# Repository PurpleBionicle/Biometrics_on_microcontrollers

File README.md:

<h1> Биометрический считыватель</h1>>
Программа имеет 2 режима: <br>
1) аутентификация - по поступающему видео перебирает датасет<br>
датасет представляет собой зашифрованную БД <br>
2) регистрация - записывается видео и из него берутся фото для датасета <br>
Оба режима поддерживают ip-камеры с помощью протокола rtsp <br>
Распознование сделано на opencv2 + face-recognition<br>
Также добавлена возможность проверки на liveness. Проверка осуществляется через фильтры Хаара, 
1 умеет определять только открытые глаза, другой открытые и закрытые <br>
Проект по Аппаратным средствам, так что тут же и разводка ПП / сборочный чертеж<br>
Пара фото: <br>

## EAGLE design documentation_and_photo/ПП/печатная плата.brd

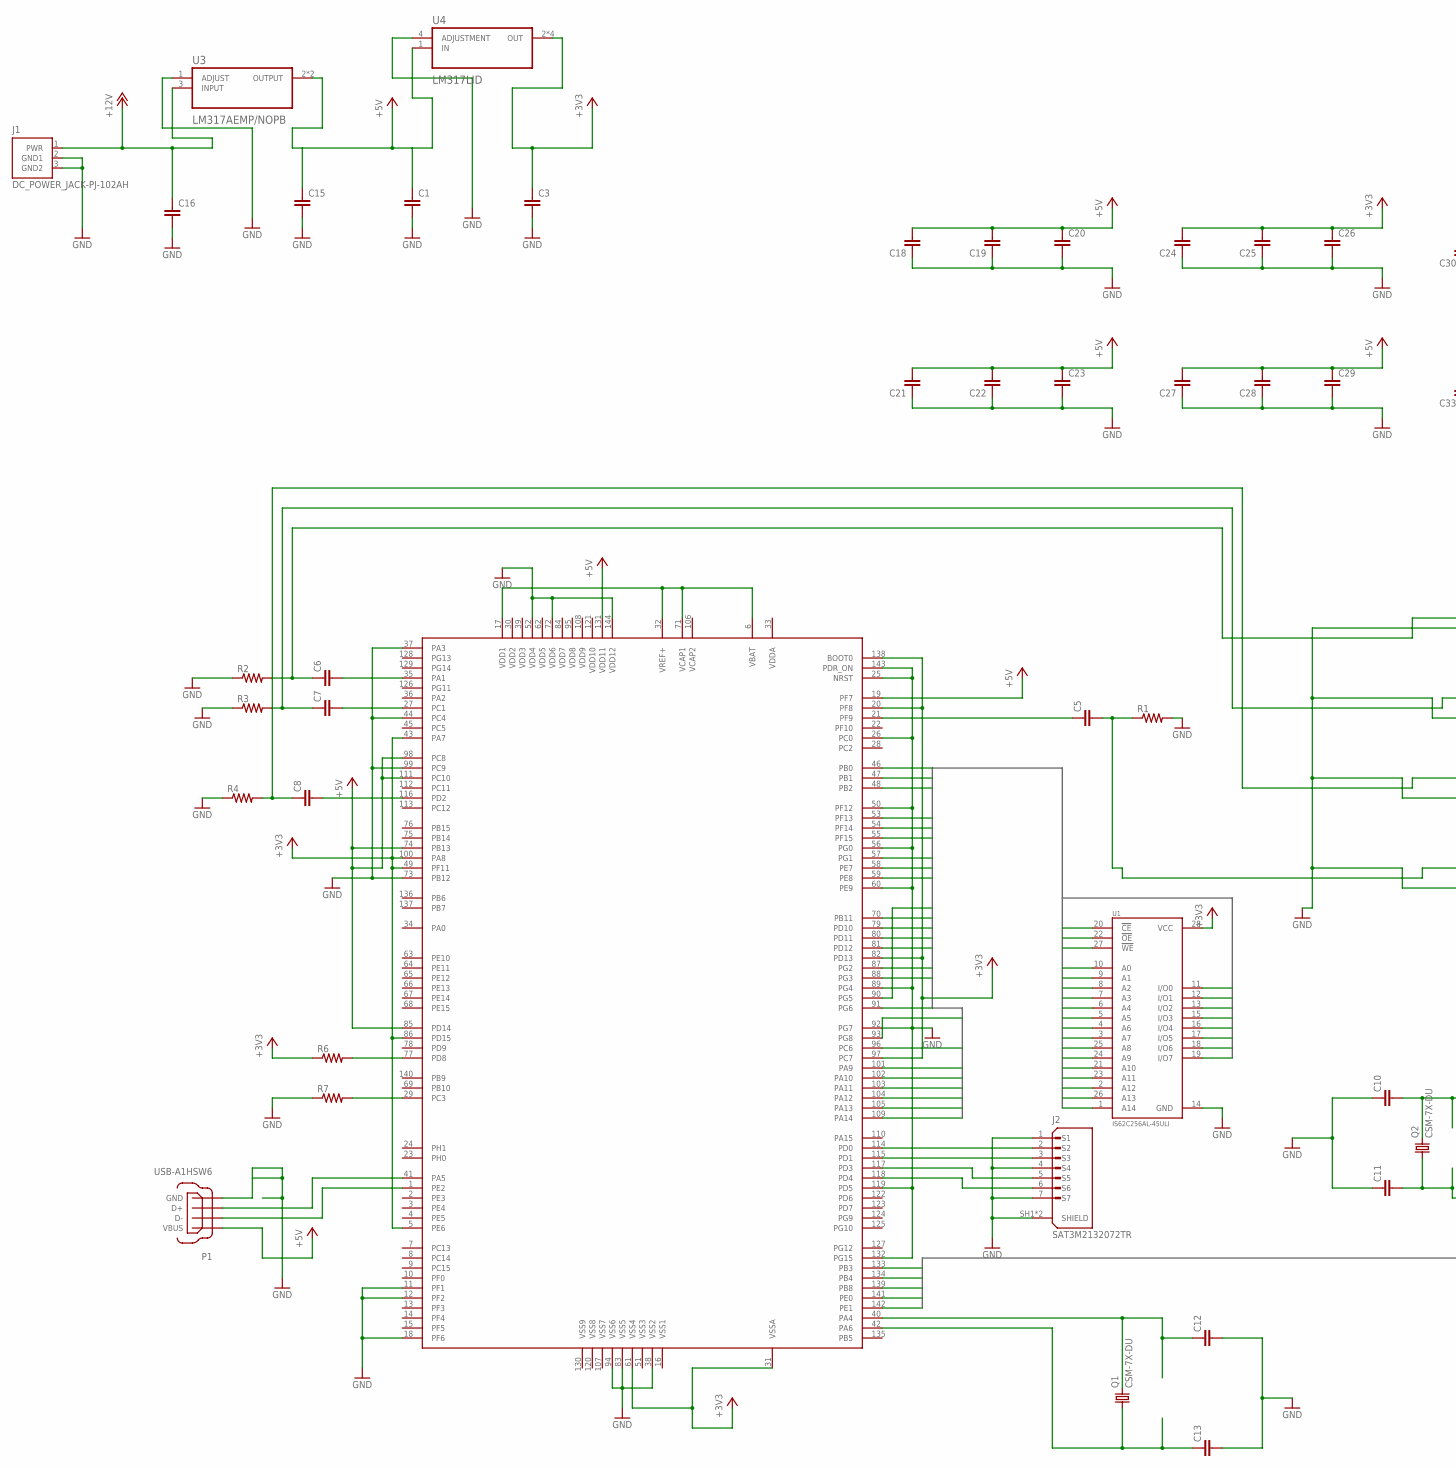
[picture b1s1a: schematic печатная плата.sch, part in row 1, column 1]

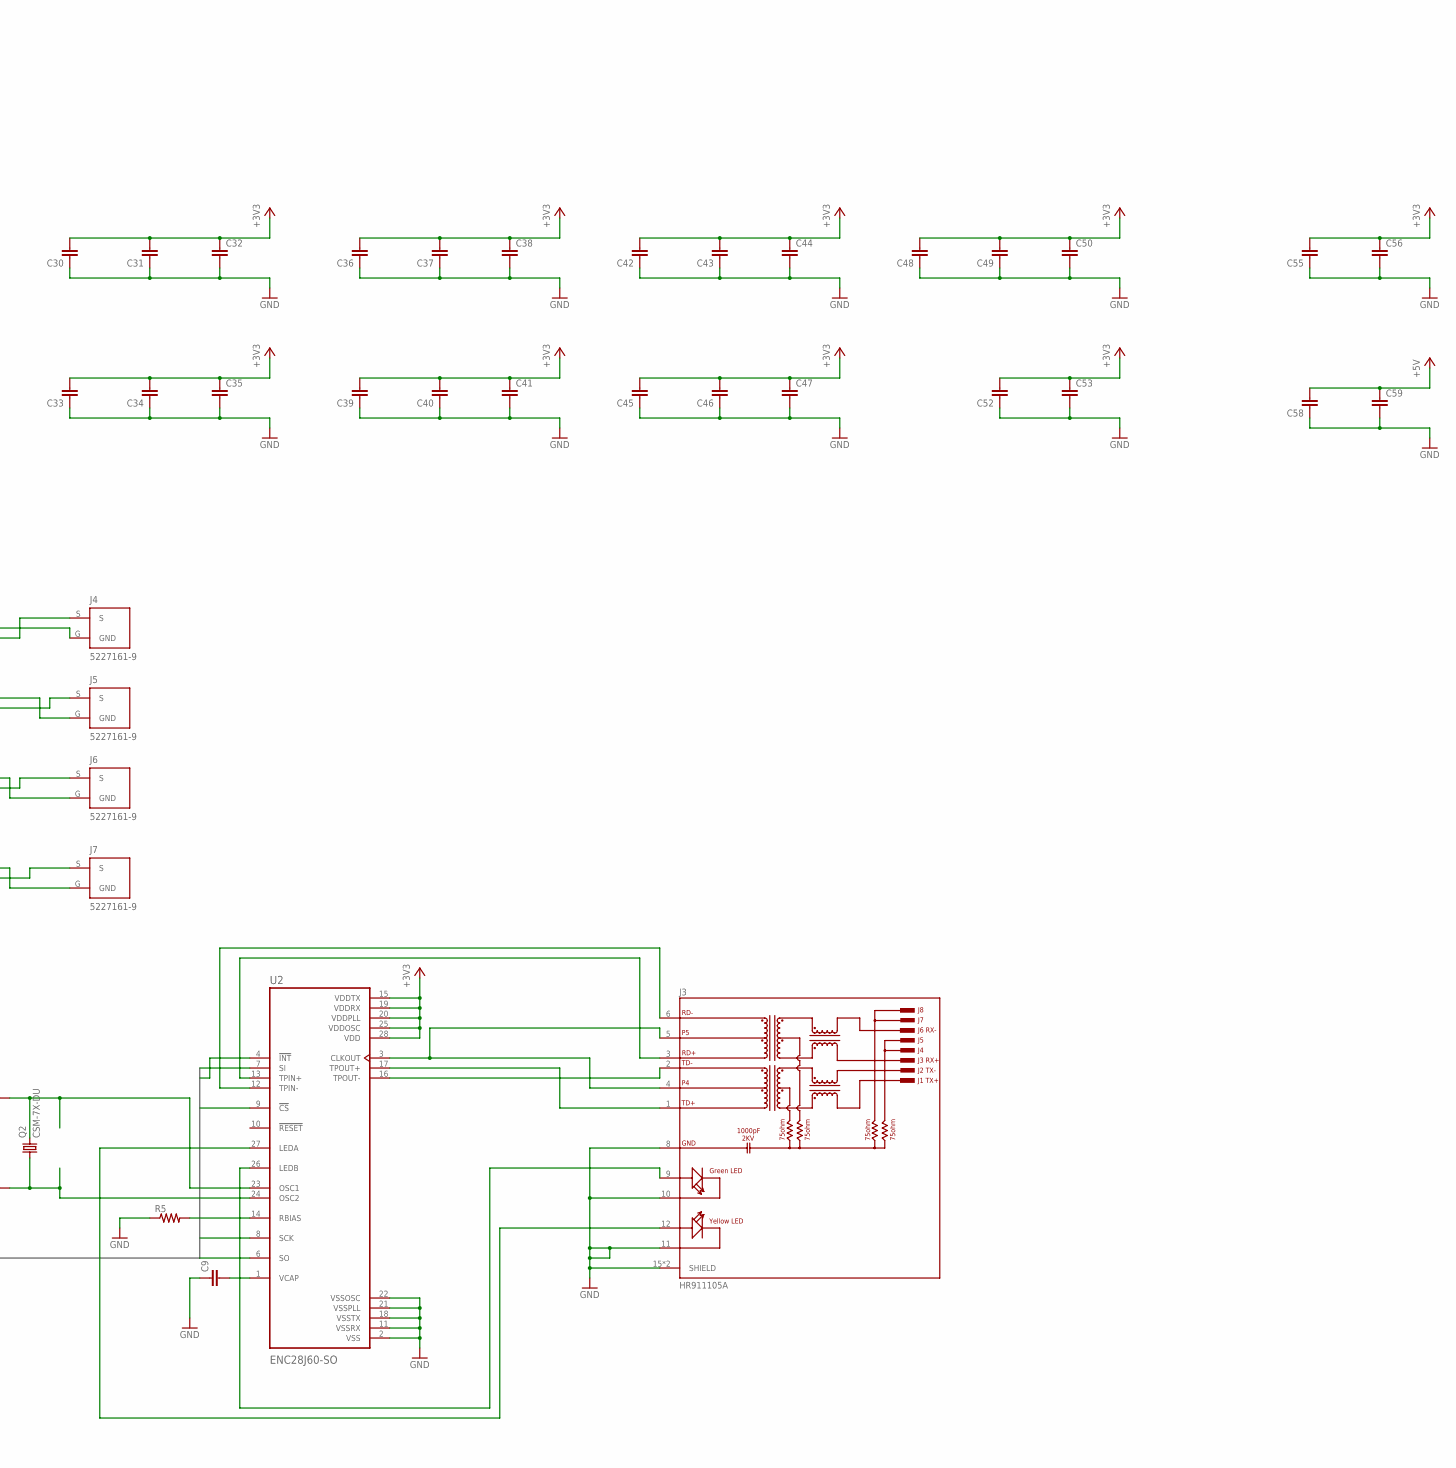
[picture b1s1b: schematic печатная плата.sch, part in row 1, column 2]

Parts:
C1, C3, C5, C6, C7, C8, C9, C10, C11, C12, C13, C15, C16, C18, C19, C20, C21, C22, C23, C24, C25, C26, C27, C28, C29, C30, C31, C32, C33, C34, C35, C36, C37, C38, C39, C40, C41, C42, C43, C44, C45, C46, C47, C48, C49, C50, C52, C53, C55, C56, C58, C59: C_0201; 0201
J1: DC_POWER_JACK-PJ-102AH; PJ-102AH
J2: SAT3M2132072TR; AMPHENOL_SAT3M2132072TR
J3: HR911105A; HANRUN_HR911105A
J4, J5, J6, J7: 5227161-9; TE_5227161-9
P1: USB-A1HSW6; OST_USB-A1HSW6
Q1, Q2: CSM-7X-DU
R1, R2, R3, R4, R5, R6, R7: R-US_M1406; M1406
U1: IS62C256AL-45ULI; SOIC127P1210X305-28N
U2: ENC28J60-SO; SOIC127P1030X265-28N
U3: LM317AEMP/NOPB; SOT230P700X180-4N
U4: LM317LID; SOIC127P599X175-8N
U$1: STM32F4Z_144PIN; LQFP144

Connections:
+3V3: C3.1, C24.2, C25.2, C26.1, C30.2, C31.2, C32.1, C33.2, C34.2, C35.1, C36.2, C37.2, C38.1, C39.2, C40.2, C41.1, C42.2, C43.2, C44.1, C45.2, C46.2, C47.1, C48.2, C49.2, C50.1, C52.2, C53.1, C55.2, C56.1, R6.1, U1.28 (VCC), U2.15 (VDDTX), U2.19 (VDDRX), U2.20 (VDDPLL), U2.25 (VDDOSC), U2.28 (VDD), U4.2 (OUT), U4.3 (OUT), U4.6 (OUT), U4.7 (OUT), U$1.5 (PE6), U$1.20 (PF8), U$1.31 (VSSA), U$1.43 (PA7), U$1.49 (PF11), U$1.61 (VSS4), U$1.82 (PD13), U$1.86 (PD15), U$1.97 (PC7), U$1.100 (PA8), U$1.138 (BOOT0)
+5V: C1.1, C18.2, C19.2, C20.1, C21.2, C22.2, C23.1, C27.2, C28.2, C29.1, C58.2, C59.1, P1.1 (VBUS), U3.2 (OUTPUT), U3.4 (OUTPUT), U4.1 (IN), U$1.19 (PF7), U$1.74 (PB13), U$1.85 (PD14), U$1.98 (PC8), U$1.111 (PC10), U$1.131 (VDD11)
+5V1: C15.1
+12V: C16.1, J1.1 (PWR), U3.3 (INPUT)
A1: U2.6 (SO), U$1.133 (PB3)
A2: U2.8 (SCK), U$1.134 (PB4)
A3: U2.9 (!CS), U$1.139 (PB8)
A4: U2.7 (SI), U$1.141 (PE0)
A5: U2.4 (!INT), U$1.142 (PE1)
D0: U$1.46 (PB0)
D1: U1.20 (!CE)
D2: U1.22 (!OE), U$1.47 (PB1), U$1.48 (PB2)
D3: U1.27 (!WE), U$1.53 (PF13)
D4: U1.10 (A0), U$1.54 (PF14)
D5: U1.9 (A1), U$1.55 (PF15)
D6: U1.8 (A2), U$1.57 (PG1)
D7: U1.7 (A3), U$1.58 (PE7)
D8: U1.6 (A4), U$1.59 (PE8)
D9: U1.5 (A5), U$1.70 (PB11)
D10: U1.4 (A6), U$1.79 (PD10)
D11: U1.3 (A7), U$1.80 (PD11)
D12: U1.25 (A8), U$1.81 (PD12)
D13: U1.24 (A9), U$1.87 (PG2)
D14: U1.21 (A10), U$1.88 (PG3)
D15: U1.23 (A11)
D16: U1.2 (A12), U$1.91 (PG6)
D17: U1.26 (A13), U$1.93 (PG8)
D18: U1.1 (A14), U$1.96 (PC6)
D19: U1.11 (I/O0), U$1.101 (PA9)
D20: U1.12 (I/O1)
D21: U1.13 (I/O2), U$1.102 (PA10)
D22: U1.15 (I/O3), U$1.103 (PA11)
D23: U1.16 (I/O4), U$1.104 (PA12)
D24: U1.17 (I/O5), U$1.105 (PA13)
D25: U1.18 (I/O6), U$1.109 (PA14)
D26: U1.19 (I/O7), U$1.90 (PG5)
GND: C1.2, C3.2, C9.1, C10.1, C11.1, C12.2, C13.2, C15.2, C16.2, C18.1, C19.1, C20.2, C21.1, C22.1, C23.2, C24.1, C25.1, C26.2, C27.1, C28.1, C29.2, C30.1, C31.1, C32.2, C33.1, C34.1, C35.2, C36.1, C37.1, C38.2, C39.1, C40.1, C41.2, C42.1, C43.1, C44.2, C45.1, C46.1, C47.2, C48.1, C49.1, C50.2, C52.1, C53.2, C55.1, C56.2, C58.1, C59.2, J1.2 (GND1), J1.3 (GND2), J2.1 (S1), J2.4 (S4), J2.7 (S7), J2.SH1 (SHIELD), J2.SH2 (SHIELD), J3.8 (GND), J3.10 (GC), J3.11 (YC), J3.15 (SHIELD), J3.16 (SHIELD), J4.G (GND), J5.G (GND), J6.G (GND), J7.G (GND), P1.4 (GND), R1.2, R2.1, R3.1, R4.1, R5.1, R7.1, U1.14 (GND), U2.2 (VSS), U2.11 (VSSRX), U2.18 (VSSTX), U2.21 (VSSPLL), U2.22 (VSSOSC), U3.1 (ADJUST), U4.4 (ADJUSTMENT), U$1.11 (PF1), U$1.12 (PF2), U$1.18 (PF6), U$1.25 (NRST), U$1.26 (PC0), U$1.37 (PA3), U$1.38 (VSS2), U$1.44 (PC4), U$1.50 (PF12), U$1.52 (VDD4), U$1.56 (PG0), U$1.60 (PE9), U$1.72 (VDD6), U$1.73 (PB12), U$1.83 (VSS5), U$1.89 (PG4), U$1.92 (PG7), U$1.94 (VSS6), U$1.99 (PC9), U$1.119 (PD5), U$1.132 (PG15), U$1.143 (PDR_ON), U$1.144 (VDD12)
unnamed: C5.2, J7.S, R1.1
unnamed: U$1.6 (VBAT), U$1.17 (VDD1), U$1.32 (VREF+), U$1.71 (VCAP1)
unnamed: C6.1, J4.S, R2.2
unnamed: C7.1, J5.S, R3.2
unnamed: C8.1, J6.S, R4.2
unnamed: J2.2 (S2), U$1.114 (PD0)
unnamed: C6.2, U$1.35 (PA1)
unnamed: C7.2, U$1.27 (PC1)
unnamed: C8.2, U$1.116 (PD2)
unnamed: C5.1, U$1.21 (PF9)
unnamed: J2.3 (S3), U$1.115 (PD1)
unnamed: J2.5 (S5), U$1.117 (PD3)
unnamed: J2.6 (S6), U$1.118 (PD4)
unnamed: J3.2 (TD-), U2.16 (TPOUT-)
unnamed: J3.1 (TD+), U2.17 (TPOUT+)
unnamed: J3.3 (RD+), U2.13 (TPIN+)
unnamed: J3.6 (RD-), U2.12 (TPIN-)
unnamed: C9.2, U2.1 (VCAP)
unnamed: C12.1, Q1.2, U$1.40 (PA4)
unnamed: C11.2, Q2.1, U2.24 (OSC2)
unnamed: C10.2, Q2.2, U2.23 (OSC1)
unnamed: C13.1, Q1.1, U$1.42 (PA6)
unnamed: R5.2, U2.14 (RBIAS)
unnamed: R7.2, U$1.29 (PC3)
unnamed: J3.4, J3.5, U2.3 (CLKOUT)
unnamed: R6.2, U$1.77 (PD8)
unnamed: P1.3 (D+), U$1.41 (PA5)
unnamed: P1.2 (D-), U$1.1 (PE2)
unnamed: J3.9 (GA), U2.26 (LEDB)
unnamed: J3.12 (YA), U2.27 (LEDA)

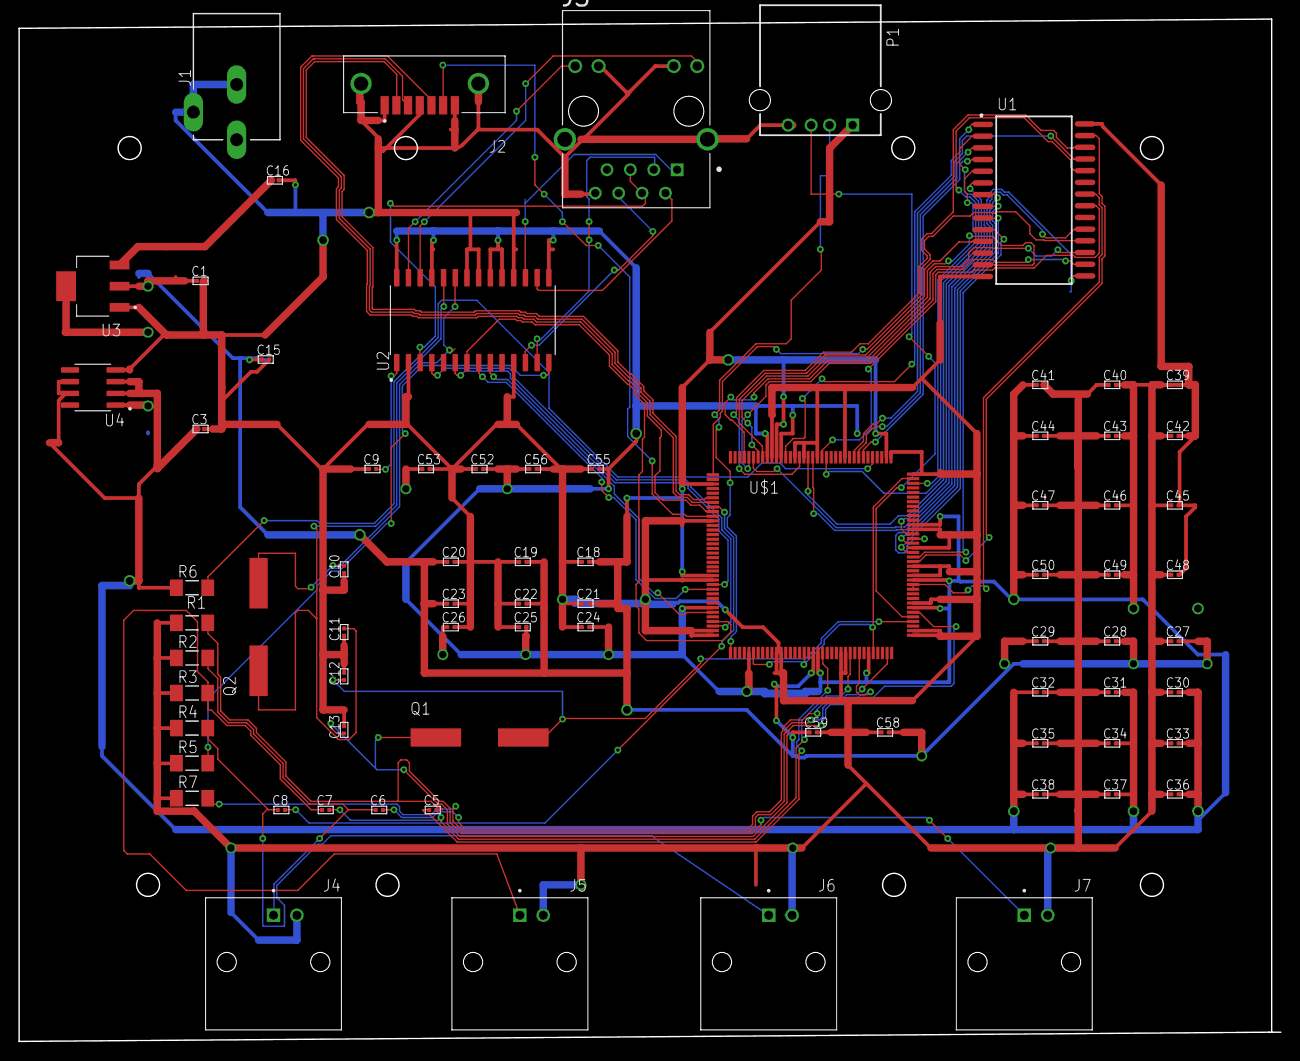
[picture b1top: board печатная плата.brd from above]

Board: 2 copper layers, 137.0 x 111.0 mm, 74 parts (0 on the bottom side), 62 nets.

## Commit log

2023-11-26 added first version of job
2023-11-26 added readme + logs
2023-12-12 with name on camera
2024-01-25 added db
2024-01-25 added biometrics with liveness
2024-01-25 little review, del old code
2024-01-25 added requirements
2024-01-25 added haara filters
2024-01-25 added logs
2024-01-25 added readme
2024-01-25 added readme and docs
